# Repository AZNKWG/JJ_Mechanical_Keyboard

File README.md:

# JJ_Mechanical_Keyboard
My repository of my 84-key mechanical keyboard.

This is my repository for an 84-key mechanical keyboard that I can use in my daily life. The reason for making this exact type of keyboard is so that it is custom to me, and because the format of it allows me to add custom changes to it to be in a more of a style of a gamer. It has a rotary encoder as a volume knob so that it is not going to be annoying to change the volume.

## CAD:

## KiCAD PCB:

## BOM:

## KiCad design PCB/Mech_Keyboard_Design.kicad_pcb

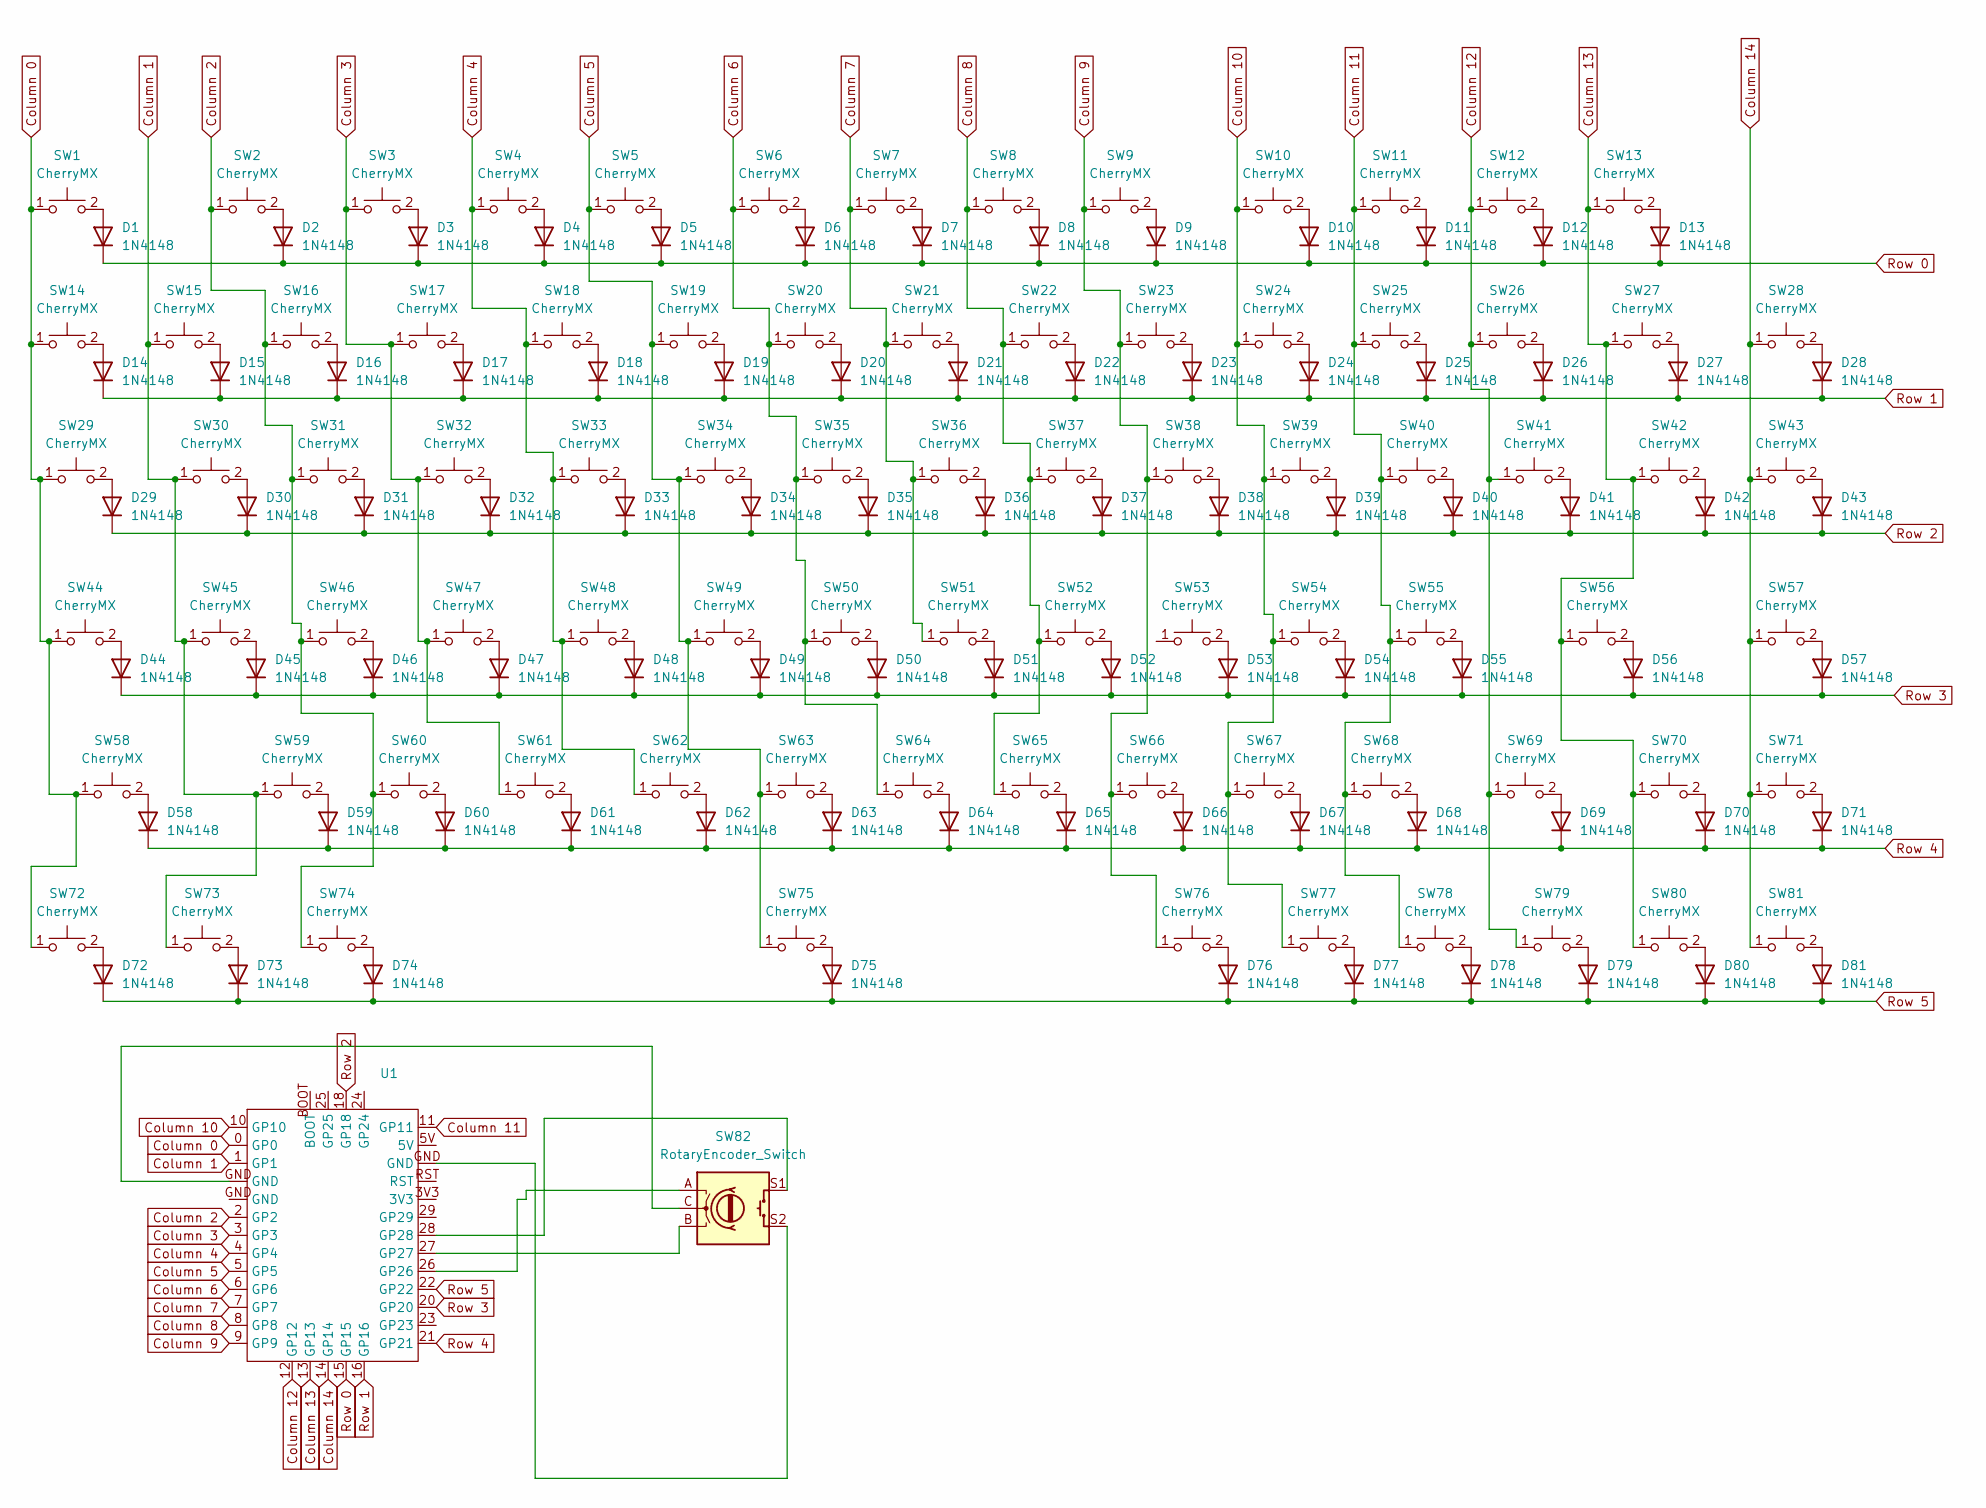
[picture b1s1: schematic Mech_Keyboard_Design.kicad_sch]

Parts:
D1, D2, D3, D4, D5, D6, D7, D8, D9, D10, D11, D12, D13, D14, D15, D16, D17, D18, D19, D20, D21, D22, D23, D24, D25, D26, D27, D28, D29, D30, D31, D32, D33, D34, D35, D36, D37, D38, D39, D40, D41, D42, D43, D44, D45, D46, D47, D48, D49, D50, D51, D52, D53, D54, D55, D56, D57, D58, D59, D60, D61, D62, D63, D64, D65, D66, D67, D68, D69, D70, D71, D72, D73, D74, D75, D76, D77, D78, D79, D80, D81: 1N4148; D_DO-35_SOD27_P7.62mm_Horizontal
SW1, SW2, SW3, SW4, SW5, SW6, SW7, SW8, SW9, SW10, SW11, SW12, SW13, SW14, SW15, SW16, SW17, SW18, SW19, SW20, SW21, SW22, SW23, SW24, SW25, SW26, SW28, SW30, SW31, SW32, SW33, SW34, SW35, SW36, SW37, SW38, SW39, SW40, SW41, SW43, SW45, SW46, SW47, SW48, SW49, SW50, SW51, SW52, SW53, SW54, SW55, SW57, SW59, SW60, SW61, SW62, SW63, SW64, SW65, SW66, SW67, SW68, SW70, SW71, SW76, SW77, SW78, SW79, SW80, SW81: CherryMX; SW_Cherry_MX_1.00u_PCB
SW27: CherryMX; SW_Cherry_MX_2.00u_PCB
SW29, SW42: CherryMX; SW_Cherry_MX_1.50u_PCB
SW44, SW69: CherryMX; SW_Cherry_MX_1.75u_PCB
SW56, SW58: CherryMX; SW_Cherry_MX_2.25u_PCB
SW72, SW73, SW74: CherryMX; SW_Cherry_MX_1.25u_PCB
SW75: CherryMX; SW_Cherry_MX_6.25u_PCB
SW82: RotaryEncoder_Switch; RotaryEncoder_Alps_EC11E-Switch_Vertical_H20mm
U1: pro_micro_rp2040

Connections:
Column 0: SW1.1, SW14.1, SW29.1, SW44.1, SW58.1, SW72.1, U1.0 (GP0)
Column 1: SW15.1, SW30.1, SW45.1, SW59.1, SW73.1, U1.1 (GP1)
Column 2: SW2.1, SW16.1, SW31.1, SW46.1, SW60.1, SW74.1, U1.2 (GP2)
Column 3: SW3.1, SW17.1, SW32.1, SW47.1, SW61.1, U1.3 (GP3)
Column 4: SW4.1, SW18.1, SW33.1, SW48.1, SW62.1, U1.4 (GP4)
Column 5: SW5.1, SW19.1, SW34.1, SW49.1, SW63.1, SW75.1, U1.5 (GP5)
Column 6: SW6.1, SW20.1, SW35.1, SW50.1, SW64.1, U1.6 (GP6)
Column 7: SW7.1, SW21.1, SW36.1, SW51.1, U1.7 (GP7)
Column 8: SW8.1, SW22.1, SW37.1, SW52.1, SW65.1, U1.8 (GP8)
Column 9: SW9.1, SW23.1, SW38.1, SW66.1, SW76.1, U1.9 (GP9)
Column 10: SW10.1, SW24.1, SW39.1, SW54.1, SW67.1, SW77.1, U1.10 (GP10)
Column 11: SW11.1, SW25.1, SW40.1, SW55.1, SW68.1, SW78.1, U1.11 (GP11)
Column 12: SW12.1, SW26.1, SW41.1, SW69.1, SW79.1, U1.12 (GP12)
Column 13: SW13.1, SW27.1, SW42.1, SW56.1, SW70.1, SW80.1, U1.13 (GP13)
Column 14: SW28.1, SW43.1, SW57.1, SW71.1, SW81.1, U1.14 (GP14)
unnamed: D1.2 (A), SW1.2
unnamed: D2.2 (A), SW2.2
unnamed: D3.2 (A), SW3.2
unnamed: D4.2 (A), SW4.2
unnamed: D5.2 (A), SW5.2
unnamed: D6.2 (A), SW6.2
unnamed: D7.2 (A), SW7.2
unnamed: D8.2 (A), SW8.2
unnamed: D9.2 (A), SW9.2
unnamed: D10.2 (A), SW10.2
unnamed: D11.2 (A), SW11.2
unnamed: D12.2 (A), SW12.2
unnamed: D13.2 (A), SW13.2
unnamed: D14.2 (A), SW14.2
unnamed: D15.2 (A), SW15.2
unnamed: D16.2 (A), SW16.2
unnamed: D17.2 (A), SW17.2
unnamed: D18.2 (A), SW18.2
unnamed: D19.2 (A), SW19.2
unnamed: D20.2 (A), SW20.2
unnamed: D21.2 (A), SW21.2
unnamed: D22.2 (A), SW22.2
unnamed: D23.2 (A), SW23.2
unnamed: D24.2 (A), SW24.2
unnamed: D25.2 (A), SW25.2
unnamed: D26.2 (A), SW26.2
unnamed: D27.2 (A), SW27.2
unnamed: D28.2 (A), SW28.2
unnamed: D29.2 (A), SW29.2
unnamed: D30.2 (A), SW30.2
unnamed: D31.2 (A), SW31.2
unnamed: D32.2 (A), SW32.2
unnamed: D33.2 (A), SW33.2
unnamed: D34.2 (A), SW34.2
unnamed: D35.2 (A), SW35.2
unnamed: D36.2 (A), SW36.2
unnamed: D37.2 (A), SW37.2
unnamed: D38.2 (A), SW38.2
unnamed: D39.2 (A), SW39.2
unnamed: D40.2 (A), SW40.2
unnamed: D41.2 (A), SW41.2
unnamed: D42.2 (A), SW42.2
unnamed: D43.2 (A), SW43.2
unnamed: D44.2 (A), SW44.2
unnamed: D45.2 (A), SW45.2
unnamed: D46.2 (A), SW46.2
unnamed: D47.2 (A), SW47.2
unnamed: D48.2 (A), SW48.2
unnamed: D49.2 (A), SW49.2
unnamed: D50.2 (A), SW50.2
unnamed: D51.2 (A), SW51.2
unnamed: D52.2 (A), SW52.2
unnamed: D53.2 (A), SW53.2
unnamed: D54.2 (A), SW54.2
unnamed: D55.2 (A), SW55.2
unnamed: D56.2 (A), SW56.2
unnamed: D57.2 (A), SW57.2
unnamed: D58.2 (A), SW58.2
unnamed: D59.2 (A), SW59.2
unnamed: D60.2 (A), SW60.2
unnamed: D61.2 (A), SW61.2
unnamed: D62.2 (A), SW62.2
unnamed: D63.2 (A), SW63.2
unnamed: D64.2 (A), SW64.2
unnamed: D65.2 (A), SW65.2
unnamed: D66.2 (A), SW66.2
unnamed: D67.2 (A), SW67.2
unnamed: D68.2 (A), SW68.2
unnamed: D69.2 (A), SW69.2
unnamed: D70.2 (A), SW70.2
unnamed: D71.2 (A), SW71.2
unnamed: D72.2 (A), SW72.2
unnamed: D73.2 (A), SW73.2
unnamed: D74.2 (A), SW74.2
unnamed: D75.2 (A), SW75.2
unnamed: D76.2 (A), SW76.2
unnamed: D77.2 (A), SW77.2
unnamed: D78.2 (A), SW78.2
unnamed: D79.2 (A), SW79.2
unnamed: D80.2 (A), SW80.2
unnamed: D81.2 (A), SW81.2
unnamed: SW82.A, U1.26 (GP26)
unnamed: SW82.B, U1.27 (GP27)
unnamed: SW82.S1, U1.28 (GP28)
Row 0: D1.1 (K), D2.1 (K), D3.1 (K), D4.1 (K), D5.1 (K), D6.1 (K), D7.1 (K), D8.1 (K), D9.1 (K), D10.1 (K), D11.1 (K), D12.1 (K), D13.1 (K), U1.15 (GP15)
Row 1: D14.1 (K), D15.1 (K), D16.1 (K), D17.1 (K), D18.1 (K), D19.1 (K), D20.1 (K), D21.1 (K), D22.1 (K), D23.1 (K), D24.1 (K), D25.1 (K), D26.1 (K), D27.1 (K), D28.1 (K), U1.16 (GP16)
Row 2: D29.1 (K), D30.1 (K), D31.1 (K), D32.1 (K), D33.1 (K), D34.1 (K), D35.1 (K), D36.1 (K), D37.1 (K), D38.1 (K), D39.1 (K), D40.1 (K), D41.1 (K), D42.1 (K), D43.1 (K), U1.18 (GP18)
Row 3: D44.1 (K), D45.1 (K), D46.1 (K), D47.1 (K), D48.1 (K), D49.1 (K), D50.1 (K), D51.1 (K), D52.1 (K), D53.1 (K), D54.1 (K), D55.1 (K), D56.1 (K), D57.1 (K), U1.20 (GP20)
Row 4: D58.1 (K), D59.1 (K), D60.1 (K), D61.1 (K), D62.1 (K), D63.1 (K), D64.1 (K), D65.1 (K), D66.1 (K), D67.1 (K), D68.1 (K), D69.1 (K), D70.1 (K), D71.1 (K), U1.21 (GP21)
Row 5: D72.1 (K), D73.1 (K), D74.1 (K), D75.1 (K), D76.1 (K), D77.1 (K), D78.1 (K), D79.1 (K), D80.1 (K), D81.1 (K), U1.22 (GP22)

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
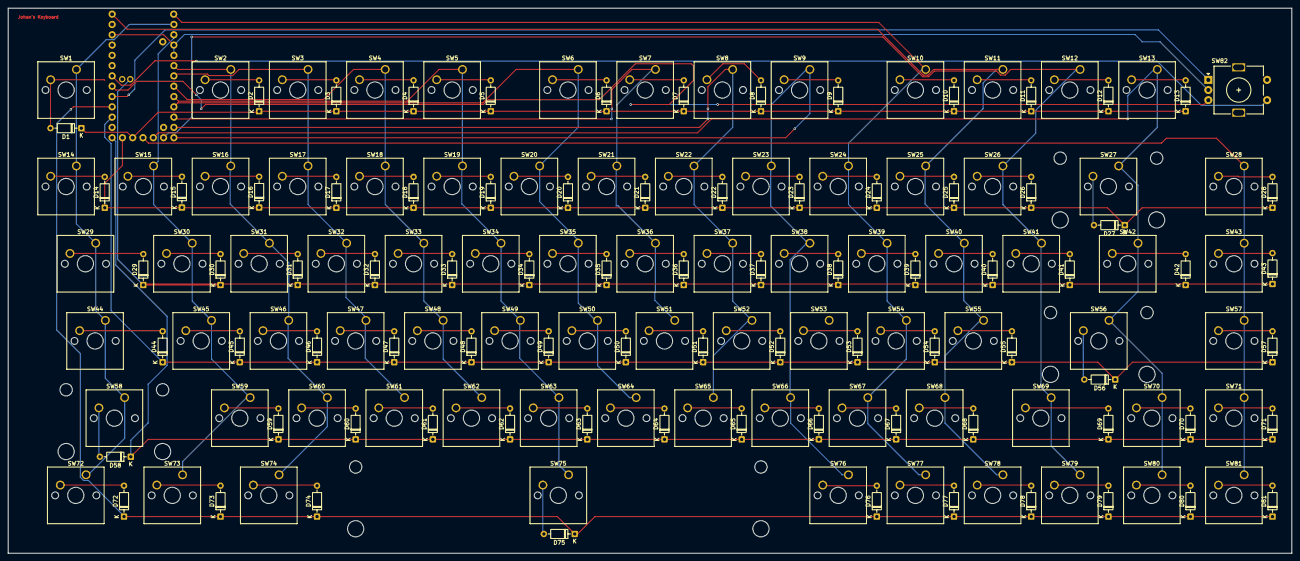
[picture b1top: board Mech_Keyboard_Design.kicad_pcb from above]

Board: 2 copper layers, 316.7 x 134.5 mm, 164 parts (1 on the bottom side), 106 nets.

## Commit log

2026-02-27 Create Mechanical_KeyboardFirmware
2026-02-27 Create Placeholder
2026-02-27 Rename Mechanical_KeyboardFirmware to Placeholder
2026-02-28 Create Firmware
2026-02-28 Rename Screenshot 2026-02-27 220812.png to JLCPCB Order
2026-03-22 Create placholder
2026-03-27 Added Final_Mech_Case.step file
